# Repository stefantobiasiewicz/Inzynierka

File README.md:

# Inzynierka

Add this folder to nrf zigbee sdk to run make command

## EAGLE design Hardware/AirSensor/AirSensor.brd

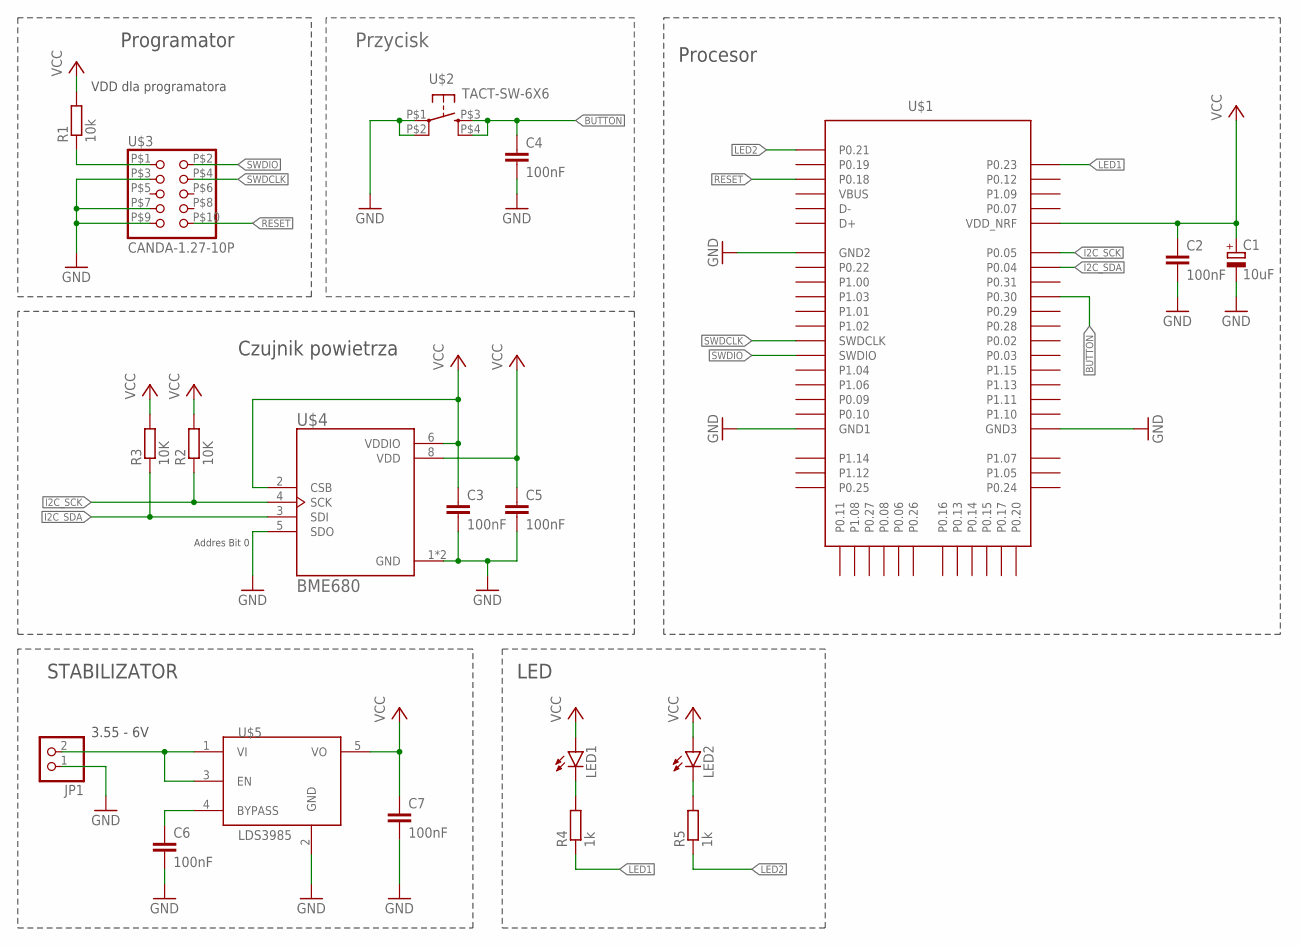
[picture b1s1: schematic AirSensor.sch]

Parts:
C1: 10uF; CT6032
C2, C3, C4, C5, C6, C7: 100nF; C0805K
JP1: PINHD-1X2; 1X02
LED1, LED2: LEDCHIPLED_0603; CHIPLED_0603
R1: 10k; R0603
R2, R3: 10K; R0603
R4, R5: 1k; R0603
U$1: HOLYIOT_18010; PCBCOMPONENT_1
U$2: TACT-SW-6X6; 6X6-TACT-SWITCH-SMD
U$3: CANDA-1.27-10P; CON-1.27-CANDA
U$4: BME680; PSON80P300X300X100-8N
U$5: LDS3985; SOT23-5

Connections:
BUTTON: C4.1, U$1.P0.30, U$2.P$3 (S), U$2.P$4 (S1)
GND: C1.-, C2.2, C3.2, C4.2, C5.2, C6.2, C7.2, JP1.1, U$1.GND (GND1), U$1.GND1 (GND2), U$1.GND2 (GND3), U$2.P$1, U$2.P$2 (P1), U$3.P$3 (3), U$3.P$7 (7), U$3.P$9 (9), U$4.1 (GND), U$4.5 (SDO), U$4.7 (GND), U$5.2 (GND)
I2C_SCK: R2.1, U$1.P0.05, U$4.4 (SCK)
I2C_SDA: R3.1, U$1.P0.04, U$4.3 (SDI)
LED1: R4.1, U$1.P0.23
LED2: R5.1, U$1.P0.21
unnamed: R1.1, U$3.P$1 (1)
unnamed: JP1.2, U$5.1 (VI), U$5.3 (EN)
unnamed: C6.1, U$5.4 (BYPASS)
unnamed: LED1.C, R4.2
unnamed: LED2.C, R5.2
RESET: U$1.P0.18, U$3.P$10 (10)
SWDCLK: U$1.SWDCLK, U$3.P$4 (4)
SWDIO: U$1.SWDIO, U$3.P$2 (2)
VCC: C1.+, C2.1, C3.1, C5.1, C7.1, LED1.A, LED2.A, R1.2, R2.2, R3.2, U$1.VDD_NRF, U$4.2 (CSB), U$4.6 (VDDIO), U$4.8 (VDD), U$5.5 (VO)

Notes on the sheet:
VDD dla programatora
Programator
Procesor
Przycisk
Addres Bit 0
Czujnik powietrza
3.55 - 6V
STABILIZATOR
LED

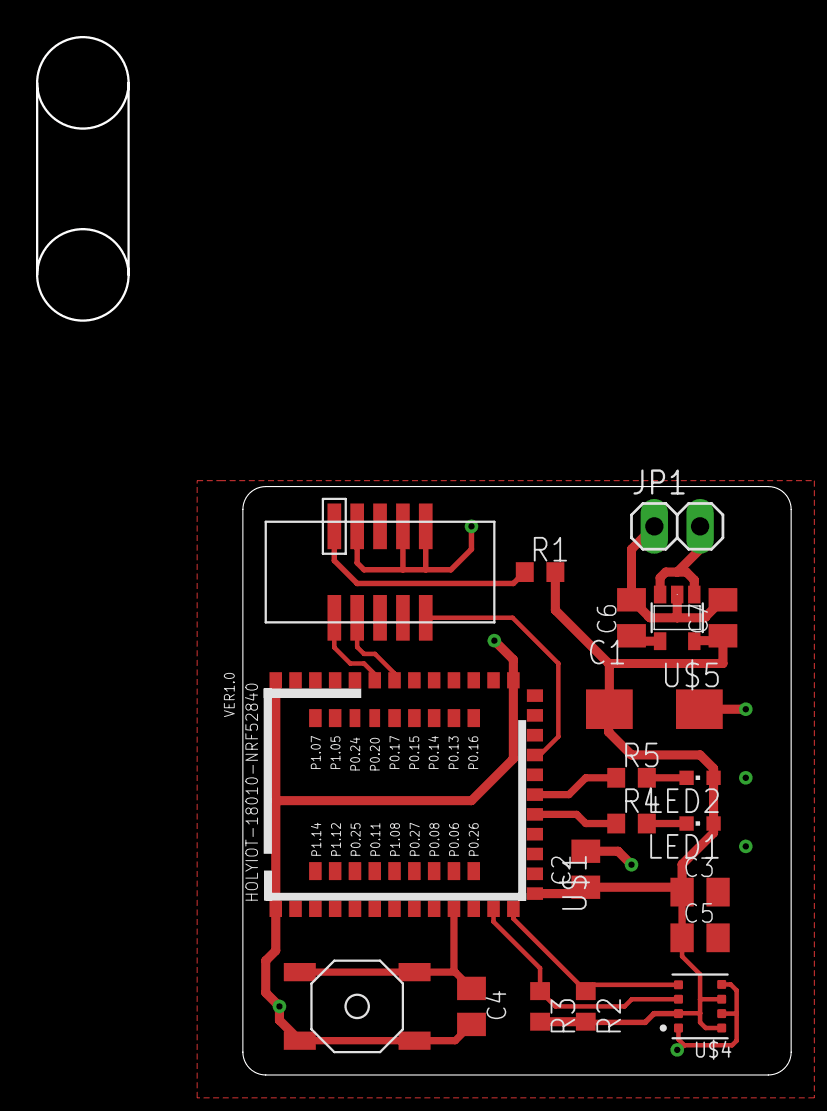
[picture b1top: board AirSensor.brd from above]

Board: 2 copper layers, 41.8 x 57.6 mm, 20 parts (0 on the bottom side), 15 nets.

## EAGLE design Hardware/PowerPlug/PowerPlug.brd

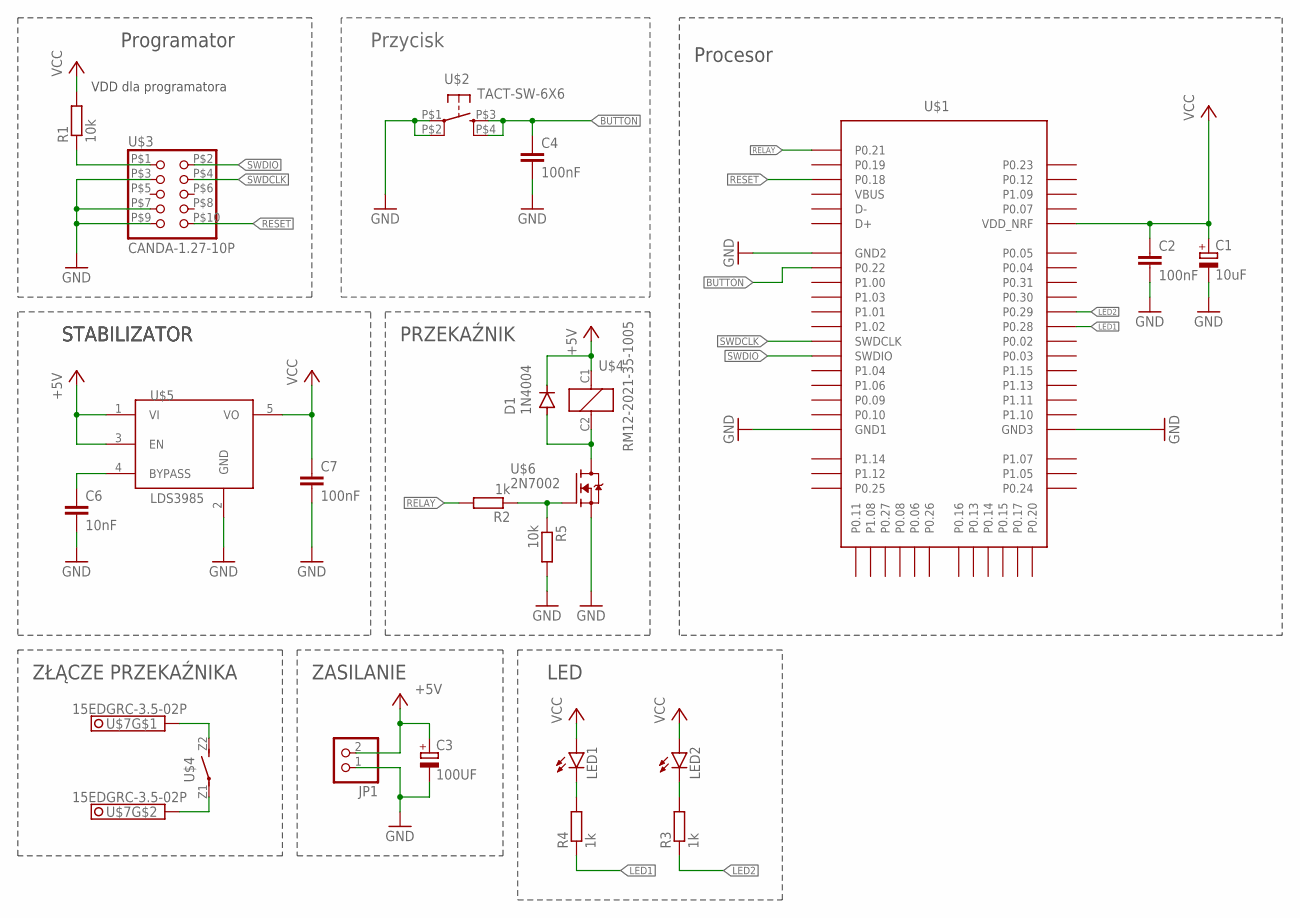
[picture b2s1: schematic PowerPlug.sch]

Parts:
C1: 10uF; CT6032
C2, C4, C7: 100nF; C0805K
C3: 100UF; 153CLV-0605
C6: 10nF; C0805K
D1: 1N4004; DO41-10
JP1: PINHD-1X2; 1X02
LED1, LED2: LEDCHIPLED_0603; CHIPLED_0603
R1, R5: 10k; R0603
R2, R3, R4: 1k; R0603
U$1: HOLYIOT_18010; PCBCOMPONENT_1
U$2: TACT-SW-6X6; 6X6-TACT-SWITCH-SMD
U$3: CANDA-1.27-10P; CON-1.27-CANDA
U$4: RM12-2021-35-1005
U$5: LDS3985; SOT23-5
U$6: 2N7002; SOT23
U$7: 15EDGRC-3.5-02P

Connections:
+5V: C3.+, D1.C, JP1.2, U$4.C1 (1), U$5.1 (VI), U$5.3 (EN)
BUTTON: C4.1, U$1.P0.22, U$2.P$3 (S), U$2.P$4 (S1)
GND: C1.-, C2.2, C3.-, C4.2, C6.2, C7.2, JP1.1, R5.2, U$1.GND (GND1), U$1.GND1 (GND2), U$1.GND2 (GND3), U$2.P$1, U$2.P$2 (P1), U$3.P$3 (3), U$3.P$7 (7), U$3.P$9 (9), U$5.2 (GND), U$6.2 (S)
LED1: R4.1, U$1.P0.28
LED2: R3.1, U$1.P0.29
unnamed: R1.1, U$3.P$1 (1)
unnamed: D1.A, U$4.C2 (2), U$6.3 (D)
unnamed: C6.1, U$5.4 (BYPASS)
unnamed: LED1.C, R4.2
unnamed: R2.1, R5.1, U$6.1 (G)
unnamed: U$4.Z2 (S), U$7.P$1
unnamed: U$4.Z1, U$7.P$2
unnamed: LED2.C, R3.2
RELAY: R2.2, U$1.P0.21
RESET: U$1.P0.18, U$3.P$10 (10)
SWDCLK: U$1.SWDCLK, U$3.P$4 (4)
SWDIO: U$1.SWDIO, U$3.P$2 (2)
VCC: C1.+, C2.1, C7.1, LED1.A, LED2.A, R1.2, U$1.VDD_NRF, U$5.5 (VO)

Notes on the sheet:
VDD dla programatora
Programator
Procesor
Przycisk
STABILIZATOR
LED
PRZEKAŹNIK
ZŁĄCZE PRZEKAŹNIKA
ZASILANIE

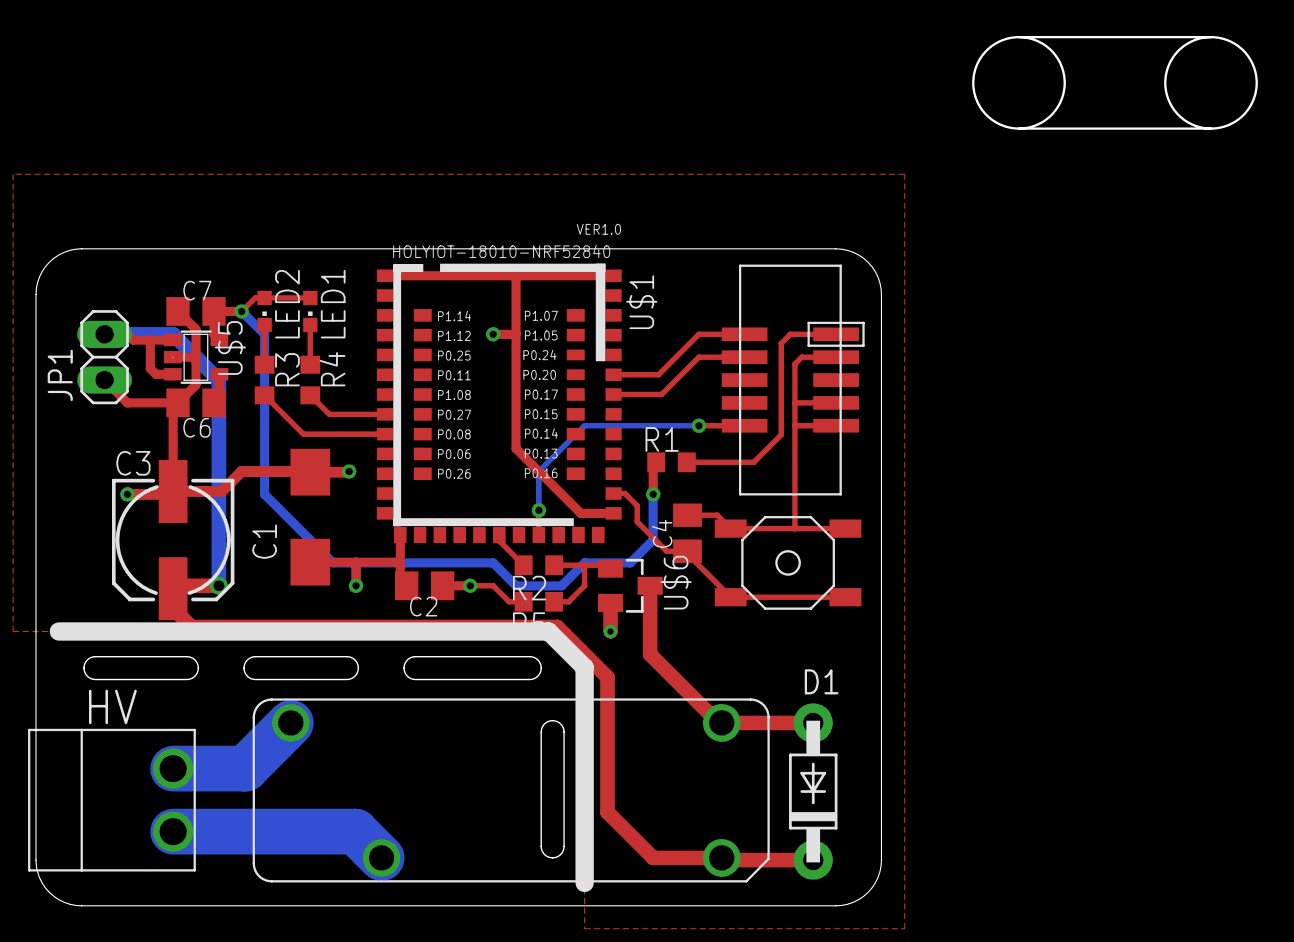
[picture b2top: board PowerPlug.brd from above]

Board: 2 copper layers, 67.8 x 48.2 mm, 22 parts (0 on the bottom side), 18 nets.

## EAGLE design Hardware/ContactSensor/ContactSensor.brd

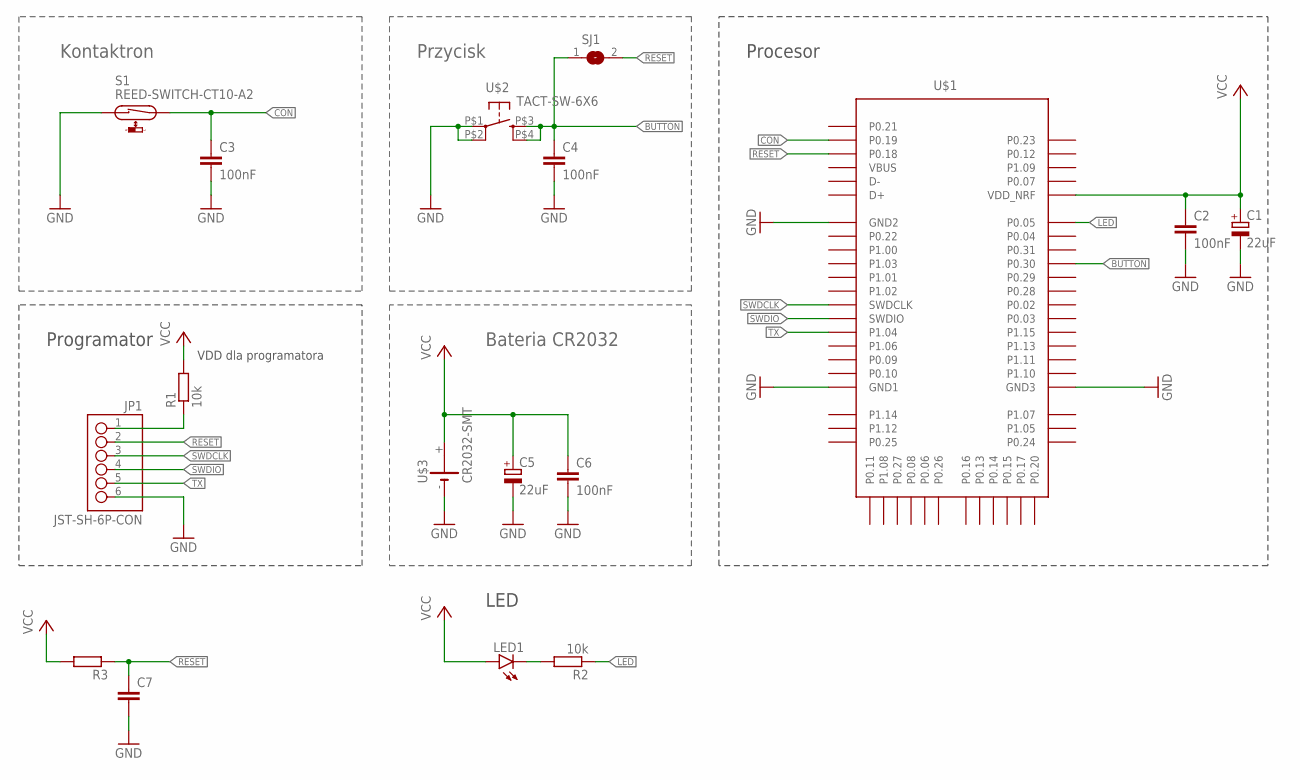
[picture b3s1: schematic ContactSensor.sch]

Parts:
C1, C5: 22uF; CT3528
C2, C3, C4, C6: 100nF; C0805K
C7: C-EUC0603K; C0603K
JP1: JST-SH-6P-CON; JST-SH-6P-FOOT
LED1: LEDCHIPLED_0603; CHIPLED_0603
R1, R2: 10k; R0603
R3: R-EU_R0402; R0402
S1: REED-SWITCH-CT10-A2; CT10-A2
SJ1: SJ
U$1: HOLYIOT_18010; PCBCOMPONENT_1
U$2: TACT-SW-6X6; 6X6-TACT-SWITCH-SMD
U$3: CR2032-SMT

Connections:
BUTTON: C4.1, SJ1.1, U$1.P0.30, U$2.P$3 (S), U$2.P$4 (S1)
CON: C3.1, S1.2, U$1.P0.19
GND: C1.-, C2.2, C3.2, C4.2, C5.-, C6.2, C7.2, JP1.6, S1.1, U$1.GND (GND1), U$1.GND1 (GND2), U$1.GND2 (GND3), U$2.P$1, U$2.P$2 (P1), U$3.-
LED: R2.1, U$1.P0.05
unnamed: JP1.1, R1.1
unnamed: LED1.C, R2.2
RESET: C7.1, JP1.2, R3.1, SJ1.2, U$1.P0.18
SWDCLK: JP1.3, U$1.SWDCLK
SWDIO: JP1.4, U$1.SWDIO
TX: JP1.5, U$1.P1.04
VCC: C1.+, C2.1, C5.+, C6.1, LED1.A, R1.2, R3.2, U$1.VDD_NRF, U$3.+

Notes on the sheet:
VDD dla programatora
Programator
Procesor
Kontaktron
Przycisk
Bateria CR2032
LED

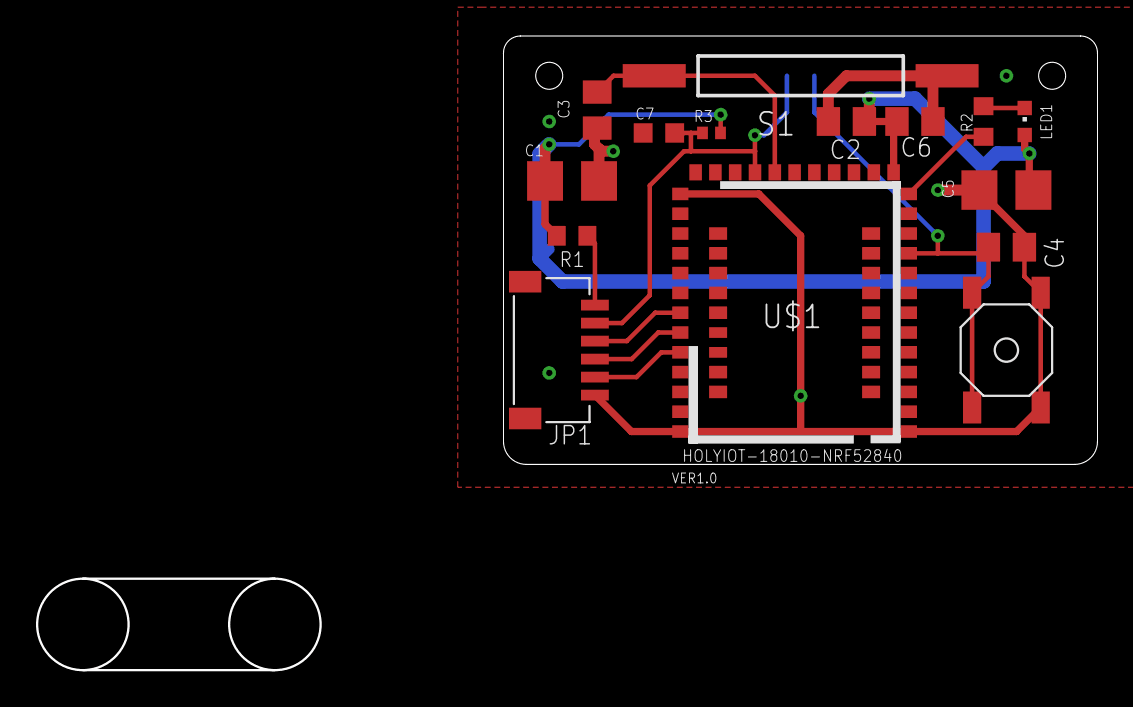
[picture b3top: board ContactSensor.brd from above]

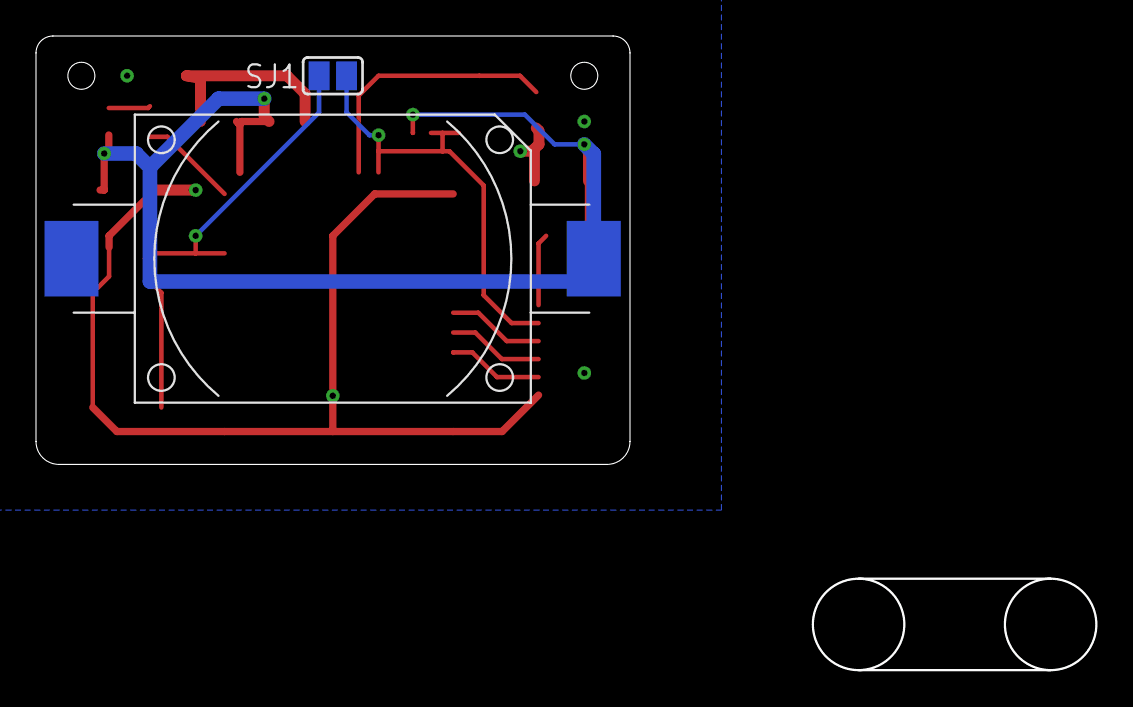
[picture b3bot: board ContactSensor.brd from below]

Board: 2 copper layers, 58.8 x 35.2 mm, 17 parts (2 on the bottom side), 11 nets.

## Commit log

2021-11-19 init
2021-11-21 BME680 project, not sending data
2021-11-23 BME680 project working
2022-01-03 contact sensor send simple command
2022-01-06 Conatct sensor working on ias Zone cluster
2022-01-06 PowerPlug work, end fixes of code needed
2022-01-07 contact sensor works after two adding device, hardocded values
2022-01-08 Air sensor done
2022-01-08 clean up workspace
2022-01-09 ContactSensor - work as SLEEP ED, PowerPlug - reset button updated
2022-01-09 ContactSensor - todo
2022-01-09 Contact Sensor - battery measure added
2022-01-09 Zigbee2mqtt converter for devices
2022-01-16 AirSensor - changed to router
2022-02-06 Hardware files added, code fixes
